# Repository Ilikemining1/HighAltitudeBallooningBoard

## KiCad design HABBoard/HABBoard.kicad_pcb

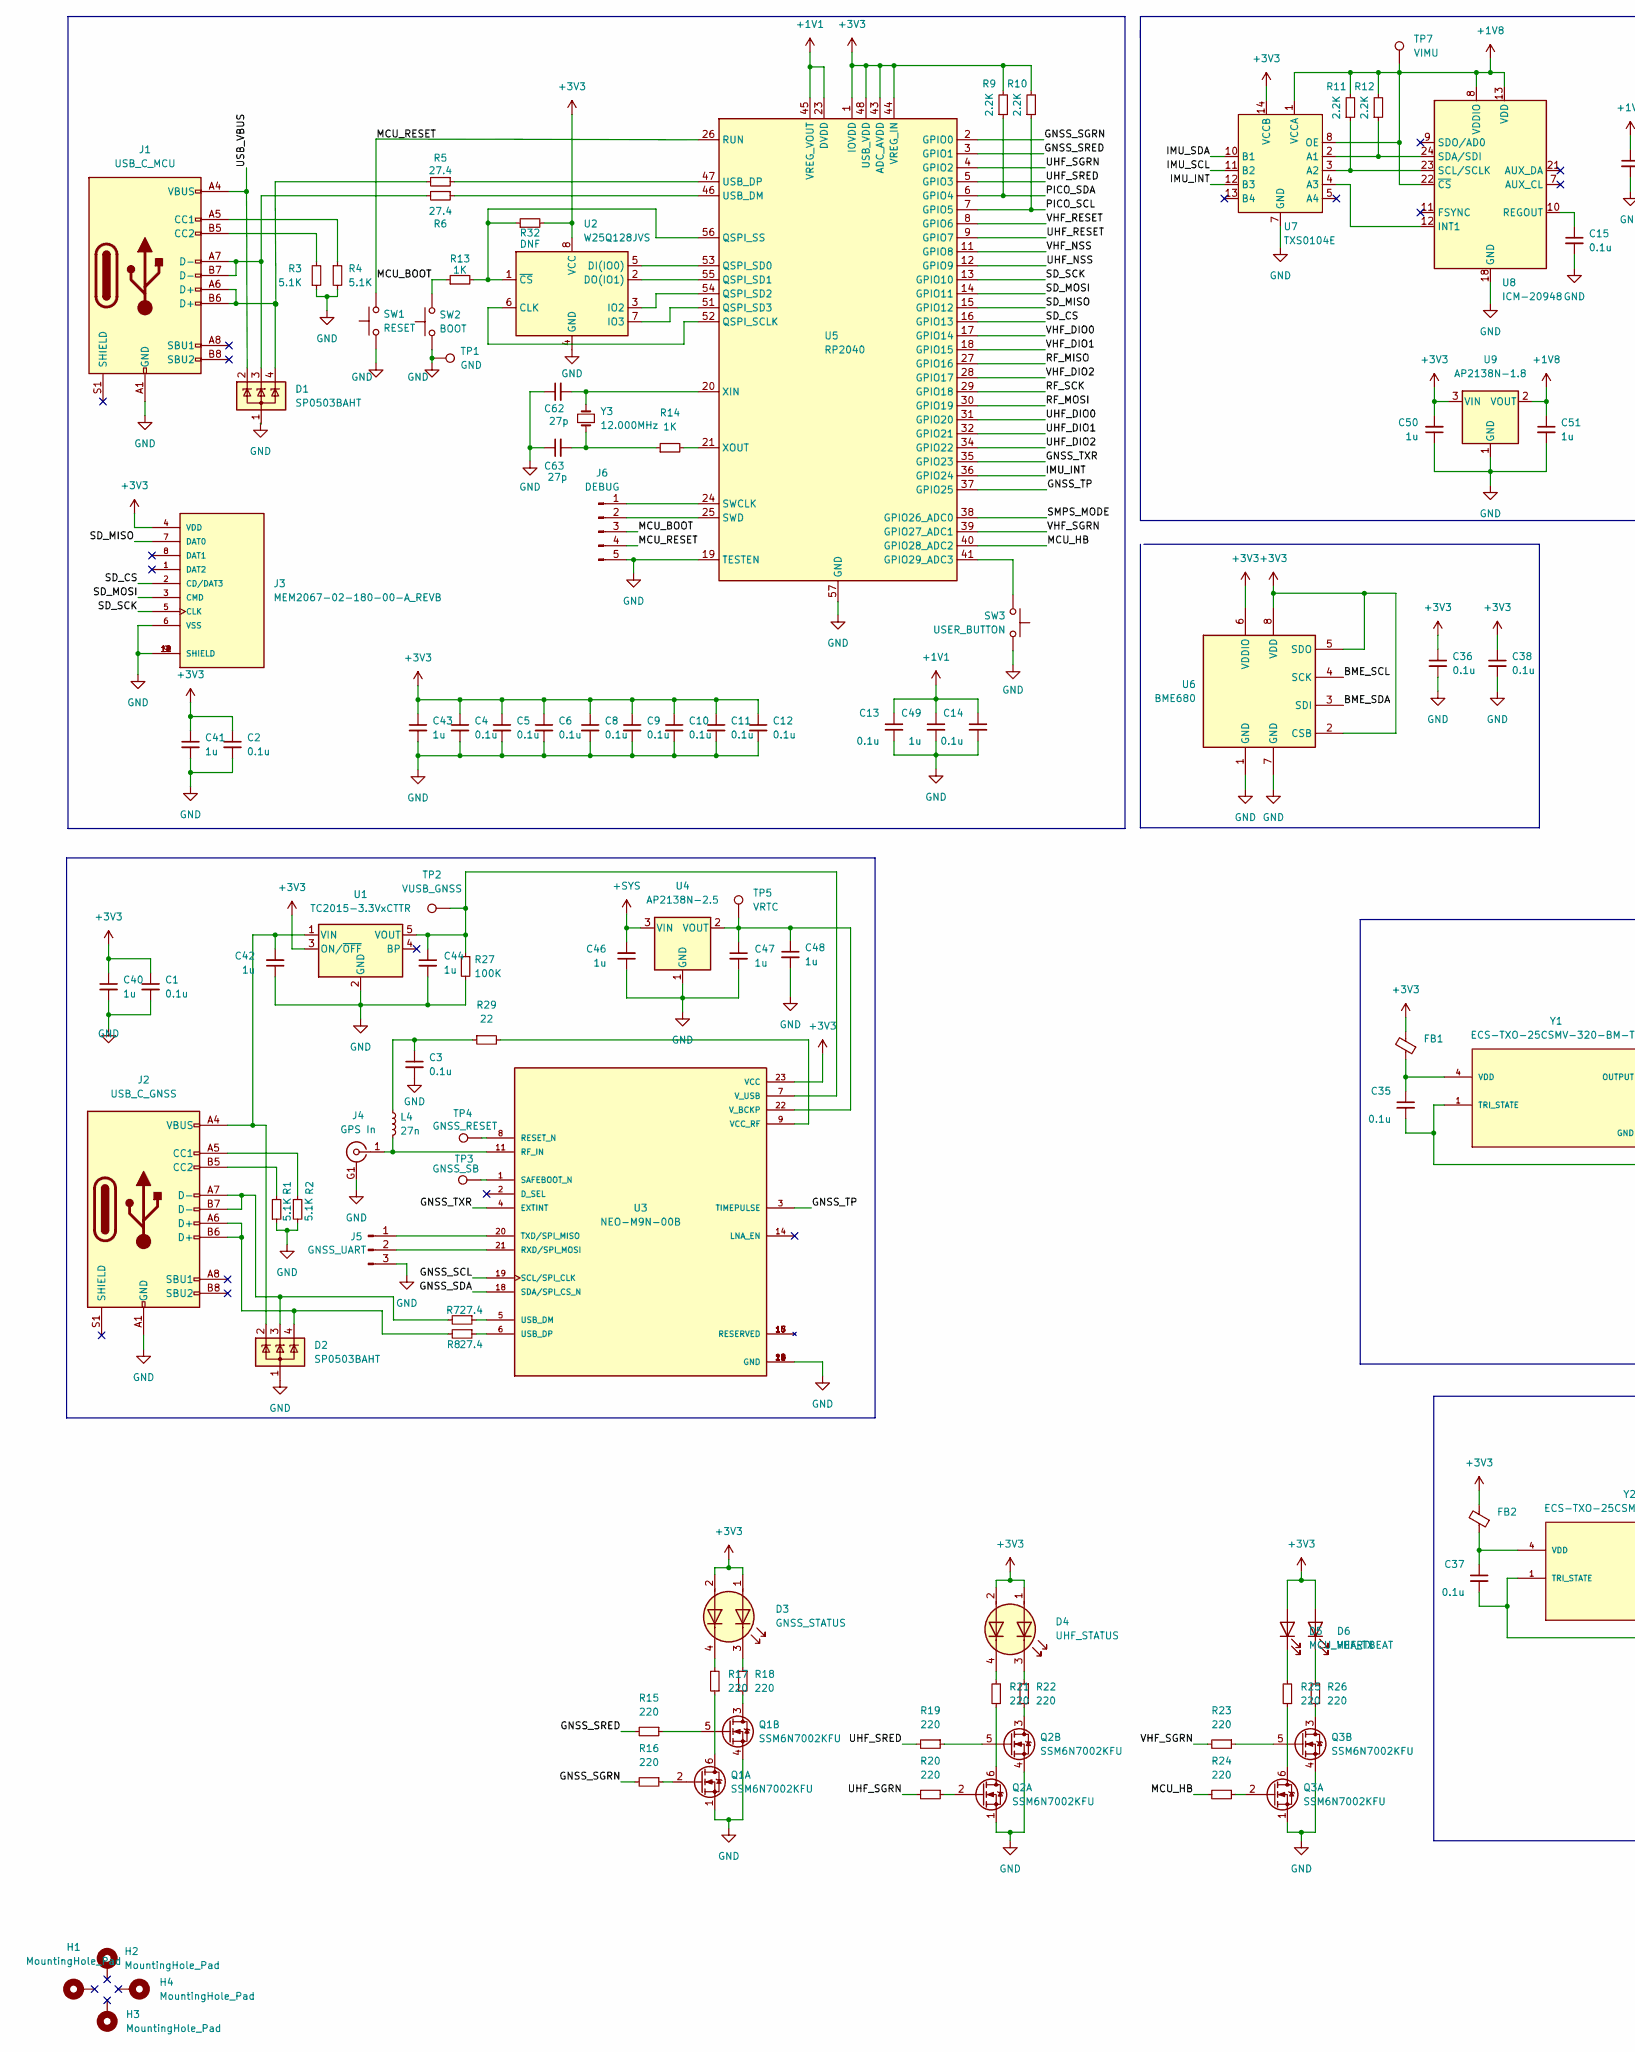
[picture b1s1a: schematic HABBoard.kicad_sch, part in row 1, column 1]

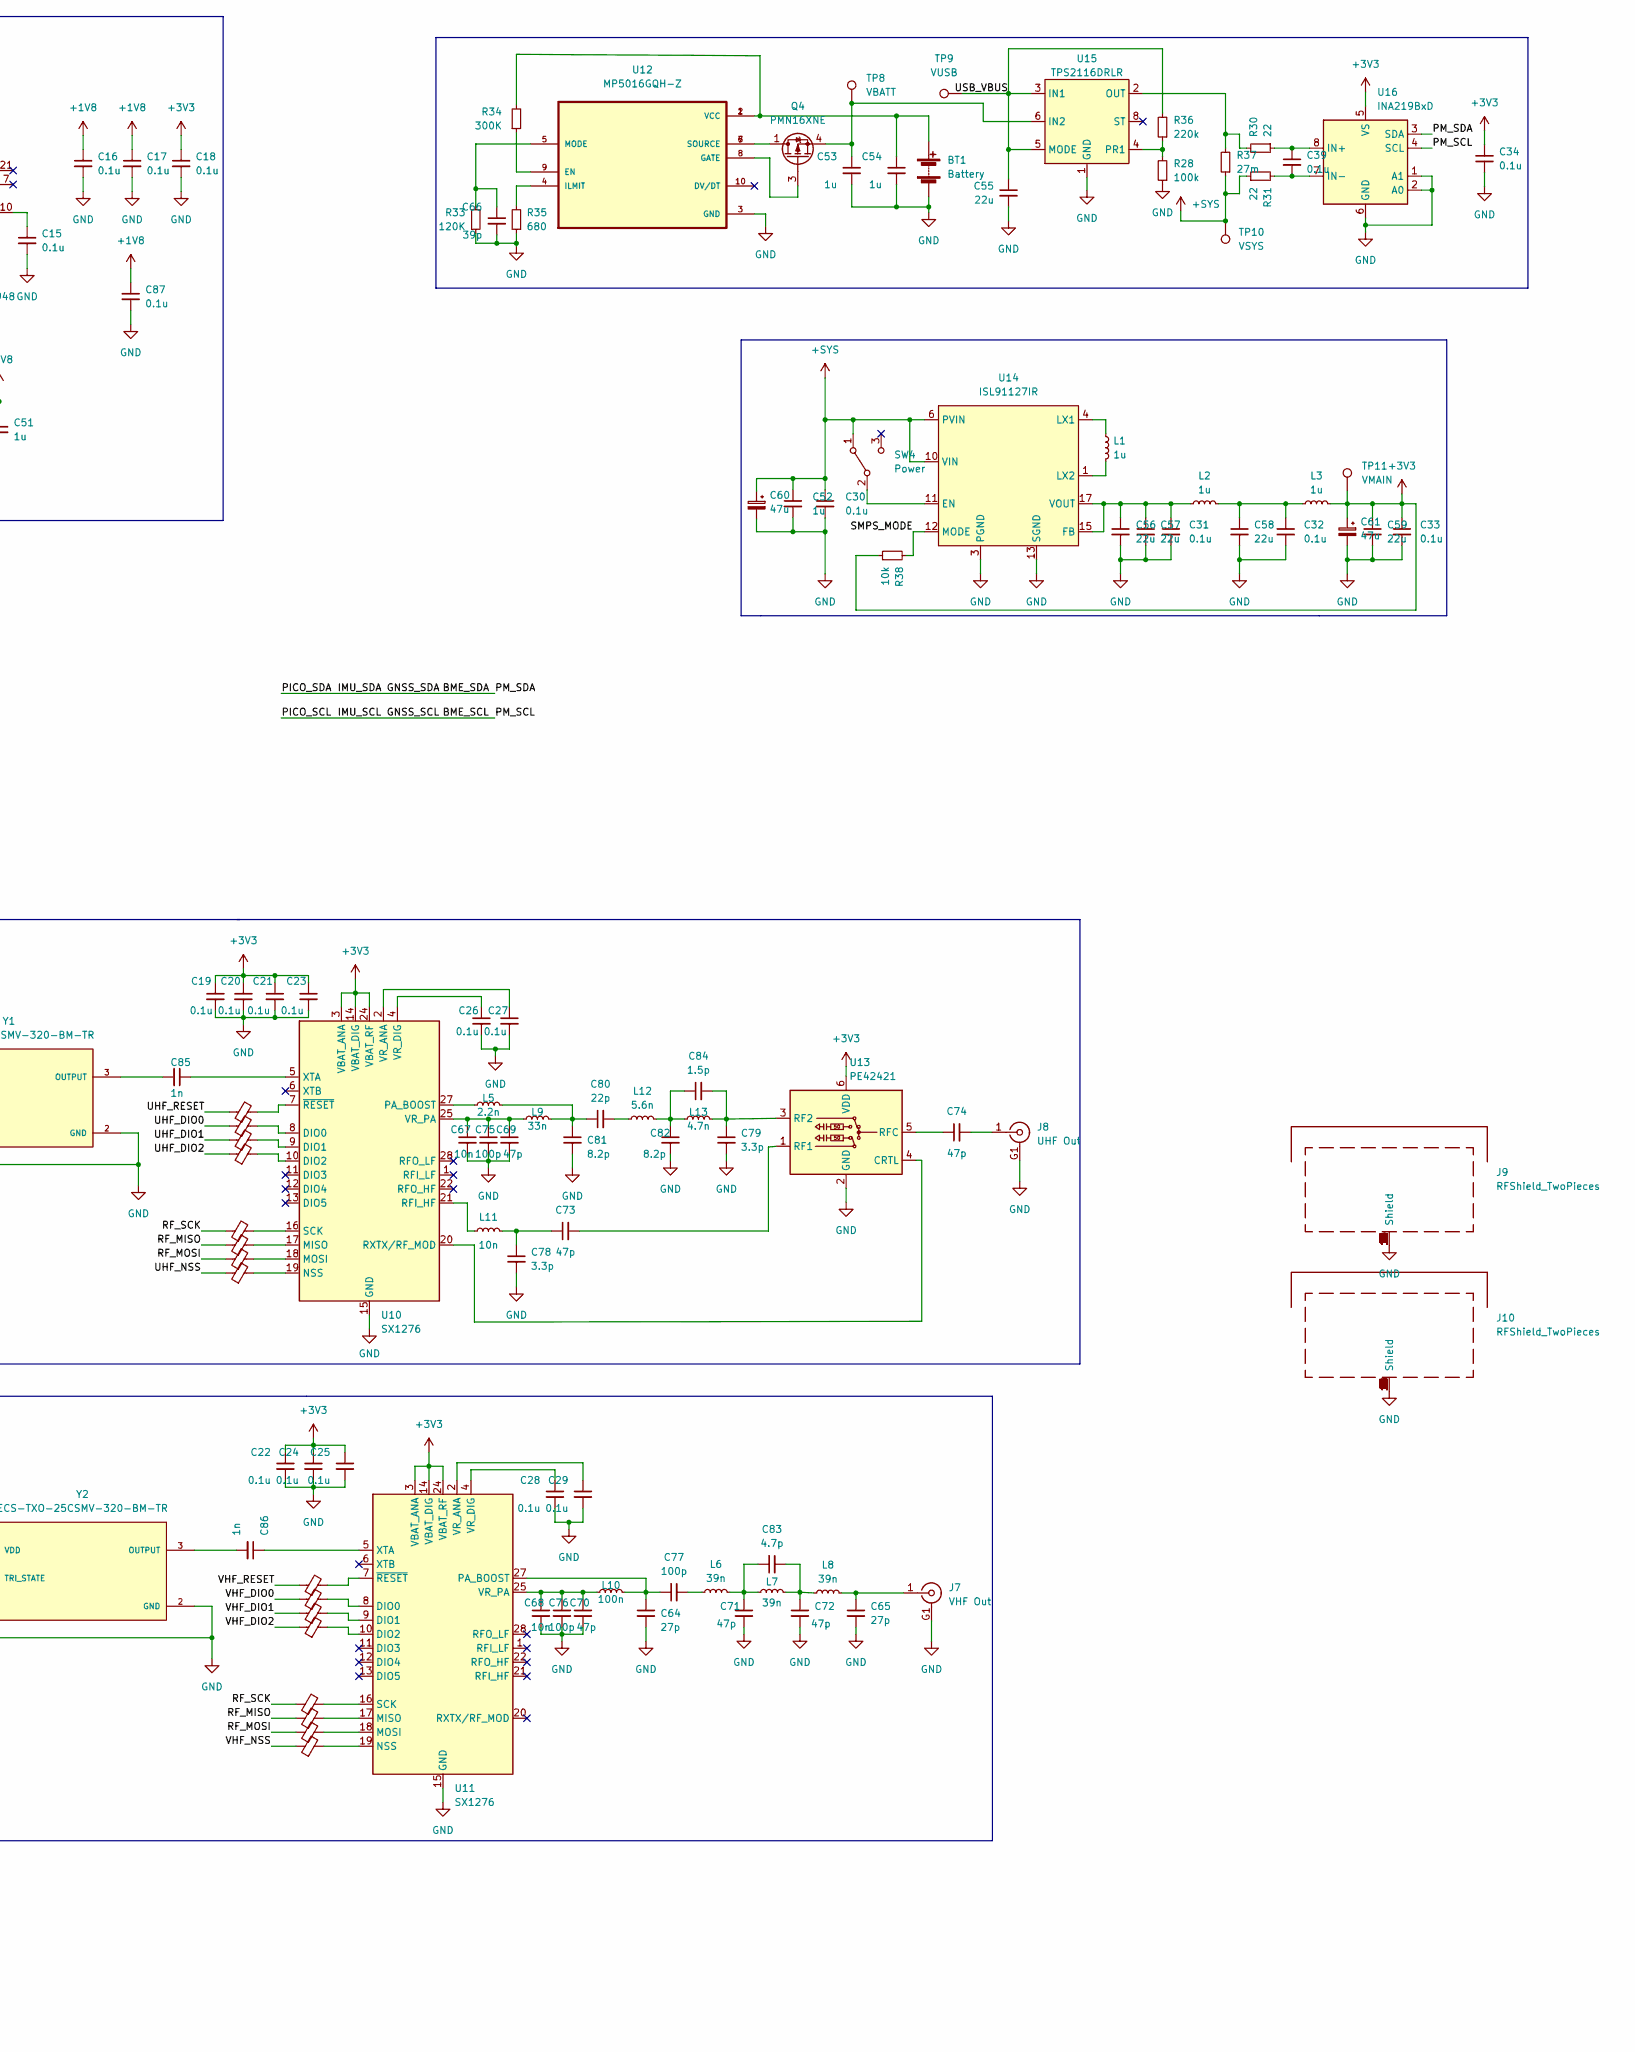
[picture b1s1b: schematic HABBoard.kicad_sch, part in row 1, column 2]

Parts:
BT1: Battery; CUI_TB002-500-02BE
C1, C2, C3, C4, C5, C6, C8, C9, C10, C11, C12, C13, C14, C15, C16, C17, C18, C19, C20, C21, C22, C23, C24, C25, C26, C27, C28, C29, C30, C31, C32, C33, C34, C35, C36, C37, C38, C39, C87: 0.1u; C_0402_1005Metric
C40, C41, C42, C43, C44, C46, C47, C48, C49, C50, C51, C52, C53, C54: 1u; C_0603_1608Metric
C55, C56, C57, C58, C59: 22u; C_0805_2012Metric
C60, C61: 47u; CP_Elec_5x5.3
C62, C63, C64, C65: 27p; C_0402_1005Metric
C66: 39p; C_0402_1005Metric
C67, C68: 10n; C_0402_1005Metric
C69, C70, C71, C72, C73, C74: 47p; C_0402_1005Metric
C75, C76, C77: 100p; C_0402_1005Metric
C78, C79: 3.3p; C_0402_1005Metric
C80: 22p; C_0402_1005Metric
C81, C82: 8.2p; C_0402_1005Metric
C83: 4.7p; C_0402_1005Metric
C84: 1.5p; C_0402_1005Metric
C85, C86: 1n; C_0402_1005Metric
D1, D2: SP0503BAHT; SOT-143
D3: GNSS_STATUS; LED_RGB_Wuerth-PLCC4_3.2x2.8mm_150141M173100
D4: UHF_STATUS; LED_RGB_Wuerth-PLCC4_3.2x2.8mm_150141M173100
D5: MCU_HEARTBEAT; LED_0603_1608Metric
D6: VHF_TX; LED_0603_1608Metric
FB1, FB2, FB3, FB4, FB5, FB7, FB8, FB9, FB10, FB11, FB12, FB13, FB14, FB15, FB16, FB17, FB18: FerriteBead_Small; L_0402_1005Metric
FB6: FB; L_0402_1005Metric
H1, H2, H3, H4: MountingHole_Pad; MountingHole_3.2mm_M3_Pad
J1: USB_C_MCU; USB_C_Receptacle_GCT_USB4085
J2: USB_C_GNSS; USB_C_Receptacle_GCT_USB4085
J3: MEM2067-02-180-00-A_REVB; GCT_MEM2067-02-180-00-A_REVB
J4: GPS In; LPRS_SMA_CONNECTOR
J5: GNSS_UART; PinHeader_1x03_P2.54mm_Vertical
J6: DEBUG; PinHeader_1x05_P2.54mm_Vertical
J7: VHF Out; LPRS_SMA_CONNECTOR
J8: UHF Out; LPRS_SMA_CONNECTOR
J9, J10: RFShield_TwoPieces; SMS409F
L1, L2, L3: 1u; L_Coilcraft_XxL4020
L4: 27n; L_0402_1005Metric
L5: 2.2n; L_0402_1005Metric
L6, L7, L8: 39n; L_0402_1005Metric
L9: 33n; L_0402_1005Metric
L10: 100n; L_0402_1005Metric
L11: 10n; L_0402_1005Metric
L12: 5.6n; L_0402_1005Metric
L13: 4.7n; L_0402_1005Metric
Q1, Q2, Q3: SSM6N7002KFU; SOT-363_SC-70-6
Q4: PMN16XNE; TSOP-6_1.65x3.05mm_P0.95mm
R1, R2, R3, R4: 5.1K; R_0402_1005Metric
R5, R6, R7, R8: 27.4; R_0402_1005Metric
R9, R10, R11, R12: 2.2K; R_0402_1005Metric
R13, R14: 1K; R_0402_1005Metric
R15, R16, R17, R18, R19, R20, R21, R22, R23, R24, R25, R26: 220; R_0402_1005Metric
R27: 100K; R_0402_1005Metric
R28: 100k; R_0402_1005Metric
R29, R30, R31: 22; R_0402_1005Metric
R32: DNF; R_0402_1005Metric
R33: 120K; R_0402_1005Metric
R34: 300K; R_0402_1005Metric
R35: 680; R_0402_1005Metric
R36: 220k; R_0402_1005Metric
R37: 27m; R_1206_3216Metric
R38: 10k; R_0402_1005Metric
SW1: RESET; PTS815SJK250SMTRLFS
SW2: BOOT; PTS815SJK250SMTRLFS
SW3: USER_BUTTON; PTS815SJK250SMTRLFS
SW4: Power; SW_JS102011SCQN
TP1: GND; TestPoint_Pad_D1.0mm
TP2: VUSB_GNSS; TestPoint_Pad_D1.0mm
TP3: GNSS_SB; TestPoint_Pad_D1.0mm
TP4: GNSS_RESET; TestPoint_Pad_D1.0mm
TP5: VRTC; TestPoint_Pad_D1.0mm
TP7: VIMU; TestPoint_Pad_D1.0mm
TP8: VBATT; TestPoint_Pad_D1.0mm
TP9: VUSB; TestPoint_Pad_D1.0mm
TP10: VSYS; TestPoint_Pad_D1.0mm
TP11: VMAIN; TestPoint_Pad_D1.0mm
U1: TC2015-3.3VxCTTR; SOT-23-5
U2: W25Q128JVS; SOIC-8_5.23x5.23mm_P1.27mm
U3: NEO-M9N-00B; XCVR_NEO-M9N-00B
U4: AP2138N-2.5; SOT-23
U5: RP2040; QFN-56-1EP_7x7mm_P0.4mm_EP3.2x3.2mm
U6: BME680; Bosch_LGA-8_3x3mm_P0.8mm_ClockwisePinNumbering
U7: TXS0104E; TSSOP-14_4.4x5mm_P0.65mm
U8: ICM-20948; InvenSense_QFN-24_3x3mm_P0.4mm
U9: AP2138N-1.8; SOT-23
U10, U11: SX1276; QFN-28-1EP_6x6mm_P0.65mm_EP4.8x4.8mm
U12: MP5016GQH-Z
U13: PE42421; SOT-363_SC-70-6
U14: ISL91127IR; QFN-20-1EP_4x4mm_P0.5mm_EP2.7x2.7mm_ThermalVias
U15: TPS2116DRLR; SOTFL50P160X60-8N
U16: INA219BxD; SOIC-8_3.9x4.9mm_P1.27mm
Y1, Y2: ECS-TXO-25CSMV-320-BM-TR; OSC_ECS-TXO-25CSMV-320-BM-TR
Y3: 12.000MHz; 445C25D12M00000

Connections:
+1V1: C13.1, C14.1, C49.1, U5.23 (DVDD), U5.45 (VREG_VOUT), U5.50 (DVDD)
+1V8: C16.1, C17.1, C51.1, C87.1, R11.2, R12.2, TP7.1, U7.1 (VCCA), U7.8 (OE), U8.8 (VDDIO), U8.13 (VDD), U8.22 (~CS), U9.2 (VOUT)
+3V3: C1.1, C2.1, C4.1, C5.1, C6.1, C8.1, C9.1, C10.1, C11.1, C12.1, C18.1, C19.1, C20.1, C21.1, C22.1, C23.1, C24.1, C25.1, C33.1, C34.1, C36.1, C38.1, C40.1, C41.1, C43.1, C50.2, C59.1, C61.1, D3.1 (A1), D3.2 (A2), D4.1 (A1), D4.2 (A2), D5.2 (A), D6.2 (A), FB1.2, FB2.2, J3.4 (VDD), L3.2, R9.2, R10.2, R32.2, R38.1, TP11.1, U1.3 (ON/~OFF), U2.8 (VCC), U3.23 (VCC), U5.1 (IOVDD), U5.10 (IOVDD), U5.22 (IOVDD), U5.33 (IOVDD), U5.42 (IOVDD), U5.43 (ADC_AVDD), U5.44 (VREG_IN), U5.48 (USB_VDD), U5.49 (IOVDD), U6.2 (CSB), U6.5 (SDO), U6.6 (VDDIO), U6.8 (VDD), U7.14 (VCCB), U9.3 (VIN), U10.3 (VBAT_ANA), U10.14 (VBAT_DIG), U10.24 (VBAT_RF), U11.3 (VBAT_ANA), U11.14 (VBAT_DIG), U11.24 (VBAT_RF), U13.6 (VDD), U16.5 (VS)
+SYS: C30.1, C46.2, C52.1, C60.1, R31.1, R37.1, SW4.1 (A), TP10.1, U4.3 (VIN), U14.6 (PVIN), U14.7 (PVIN), U14.8 (PVIN), U14.9 (PVIN), U14.10 (VIN)
/BME_SCL: R10.1, U3.19 (SCL/SPI_CLK), U5.7 (GPIO5), U6.4 (SCK), U7.11 (B2), U16.4 (SCL)
/BME_SDA: R9.1, U3.18 (SDA/SPI_CS_N), U5.6 (GPIO4), U6.3 (SDI), U7.10 (B1), U16.3 (SDA)
/GNSS_SGRN: R16.2, U5.2 (GPIO0)
/GNSS_SRED: R15.2, U5.3 (GPIO1)
/GNSS_TP: U3.3 (TIMEPULSE), U5.37 (GPIO25)
/GNSS_TXR: U3.4 (EXTINT), U5.35 (GPIO23)
/IMU_INT: U5.36 (GPIO24), U7.12 (B3)
/MCU_BOOT: J6.3, R13.1, SW2.2
/MCU_HB: R24.2, U5.40 (GPIO28_ADC2)
/MCU_RESET: J6.4, SW1.2, U5.26 (RUN)
/RF_MISO: FB4.1, FB12.1, U5.27 (GPIO16)
/RF_MOSI: FB5.1, FB13.1, U5.30 (GPIO19)
/RF_SCK: FB3.1, FB11.1, U5.29 (GPIO18)
/SD_CS: J3.2 (CD/DAT3), U5.16 (GPIO13)
/SD_MISO: J3.7 (DAT0), U5.15 (GPIO12)
/SD_MOSI: J3.3 (CMD), U5.14 (GPIO11)
/SD_SCK: J3.5 (CLK), U5.13 (GPIO10)
/SMPS_MODE: R38.2, U5.38 (GPIO26_ADC0), U14.12 (MODE)
/UHF_DIO0: FB8.1, U5.31 (GPIO20)
/UHF_DIO1: FB9.1, U5.32 (GPIO21)
/UHF_DIO2: FB10.1, U5.34 (GPIO22)
/UHF_NSS: FB6.1, U5.12 (GPIO9)
/UHF_RESET: FB7.1, U5.9 (GPIO7)
/UHF_SGRN: R20.2, U5.4 (GPIO2)
/UHF_SRED: R19.2, U5.5 (GPIO3)
/USB_VBUS: C55.1, D1.2 (K), J1.A4 (VBUS), J1.A9 (VBUS), J1.B4 (VBUS), J1.B9 (VBUS), R36.2, TP9.1, U15.3 (IN1), U15.5 (MODE)
/VHF_DIO0: FB16.1, U5.17 (GPIO14)
/VHF_DIO1: FB17.1, U5.18 (GPIO15)
/VHF_DIO2: FB18.1, U5.28 (GPIO17)
/VHF_NSS: FB14.1, U5.11 (GPIO8)
/VHF_RESET: FB15.1, U5.8 (GPIO6)
/VHF_SGRN: R23.2, U5.39 (GPIO27_ADC1)
GND: BT1.2 (-), C1.2, C2.2, C3.2, C4.2, C5.2, C6.2, C8.2, C9.2, C10.2, C11.2, C12.2, C13.2, C14.2, C15.2, C16.2, C17.2, C18.2, C19.2, C20.2, C21.2, C22.2, C23.2, C24.2, C25.2, C26.2, C27.2, C28.2, C29.2, C30.2, C31.2, C32.2, C33.2, C34.2, C35.2, C36.2, C37.2, C38.2, C40.2, C41.2, C42.1, C43.2, C44.2, C46.1, C47.2, C48.2, C49.2, C50.1, C51.2, C52.2, C53.2, C54.2, C55.2, C56.2, C57.2, C58.2, C59.2, C60.2, C61.2, C62.1, C63.1, C64.2, C65.2, C66.2, C67.2, C68.2, C69.2, C70.2, C71.2, C72.2, C75.2, C76.2, C78.2, C79.2, C81.2, C82.2, C87.2, D1.1 (A), D2.1 (A), J1.A1 (GND), J1.A12 (GND), J1.B1 (GND), J1.B12 (GND), J2.A1 (GND), J2.A12 (GND), J2.B1 (GND), J2.B12 (GND), J3.6 (VSS), J3.9 (SHIELD), J3.10 (SHIELD), J3.11 (SHIELD), J3.12 (SHIELD), J4.G1 (Ext), J4.G2 (Ext), J4.G3 (Ext), J4.G4 (Ext), J5.3, J6.5, J7.G1 (Ext), J7.G2 (Ext), J7.G3 (Ext), J7.G4 (Ext), J8.G1 (Ext), J8.G2 (Ext), J8.G3 (Ext), J8.G4 (Ext), J9.1 (Shield), J9.2 (Shield), J9.3 (Shield), J9.4 (Shield), J9.5 (Shield), J9.6 (Shield), J9.7 (Shield), J9.8 (Shield), J9.9 (Shield), J9.10 (Shield), J9.11 (Shield), J9.12 (Shield), J9.13 (Shield), J9.14 (Shield), J9.15 (Shield), J9.16 (Shield), J10.1 (Shield), J10.2 (Shield), J10.3 (Shield), J10.4 (Shield), J10.5 (Shield), J10.6 (Shield), J10.7 (Shield), J10.8 (Shield), J10.9 (Shield), J10.10 (Shield), J10.11 (Shield), J10.12 (Shield), J10.13 (Shield), J10.14 (Shield), J10.15 (Shield), J10.16 (Shield), Q1.1 (S), Q1.4 (S), Q2.1 (S), Q2.4 (S), Q3.1 (S), Q3.4 (S), R1.1, R2.2, R3.1, R4.2, R27.2, R28.1, R33.1, R35.1, SW1.1, SW2.1, SW3.1, TP1.1, U1.2 (GND), U2.4 (GND), U3.10 (GND), U3.12 (GND), U3.13 (GND), U3.24 (GND), U4.1 (GND), U5.19 (TESTEN), U5.57 (GND), U6.1 (GND), U6.7 (GND), U7.7 (GND), U8.18 (GND), U8.20 (GND), U9.1 (GND), U10.15 (GND), U10.23 (GND), U10.26 (GND), U10.29 (GND), U11.15 (GND), U11.23 (GND), U11.26 (GND), U11.29 (GND), U12.3 (GND), U13.2 (GND), U14.3 (PGND), U14.13 (SGND), U14.14 (SGND), U14.21 (PGND), U15.1 (GND), U16.1 (A1), U16.2 (A0), U16.6 (GND), Y1.1 (TRI_STATE), Y1.2 (GND), Y2.1 (TRI_STATE), Y2.2 (GND)
unnamed: BT1.1 (+), C54.1, R34.2, U12.1 (VCC), U12.2 (VCC)
unnamed: C3.1, L4.1, R29.1
unnamed: C15.1, U8.10 (REGOUT)
unnamed: C26.1, U10.4 (VR_DIG)
unnamed: C27.1, U10.2 (VR_ANA)
unnamed: C28.1, U11.4 (VR_DIG)
unnamed: C29.1, U11.2 (VR_ANA)
unnamed: C31.1, C56.1, C57.1, L2.1, U14.15 (FB), U14.17 (VOUT), U14.18 (VOUT), U14.19 (VOUT), U14.20 (VOUT)
unnamed: C32.1, C58.1, L2.2, L3.1
unnamed: C35.1, FB1.1, Y1.4 (VDD)
unnamed: C37.1, FB2.1, Y2.4 (VDD)
unnamed: C39.1, R30.1, U16.8 (IN+)
unnamed: C39.2, R31.2, U16.7 (IN-)
unnamed: C42.2, D2.2 (K), J2.A4 (VBUS), J2.A9 (VBUS), J2.B4 (VBUS), J2.B9 (VBUS), U1.1 (VIN)
unnamed: C44.1, R27.1, TP2.1, U1.5 (VOUT), U3.7 (V_USB)
unnamed: C47.1, C48.1, TP5.1, U3.22 (V_BCKP), U4.2 (VOUT)
unnamed: C53.1, Q4.4 (S), TP8.1, U15.6 (IN2)
unnamed: C62.2, U5.20 (XIN), Y3.2
unnamed: C63.2, R14.1, Y3.1
unnamed: C64.1, C77.1, L10.2, U11.27 (PA_BOOST)
unnamed: C65.1, J7.1 (In), L8.2
unnamed: C66.1, R33.2, U12.5 (MODE)
unnamed: C67.1, C69.1, C75.1, L9.1, U10.25 (VR_PA)
unnamed: C68.1, C70.1, C76.1, L10.1, U11.25 (VR_PA)
unnamed: C71.1, C83.1, L6.2, L7.1
unnamed: C72.1, C83.2, L7.2, L8.1
unnamed: C73.1, C78.1, L11.2
unnamed: C73.2, U13.1 (RF1)
unnamed: C74.1, U13.5 (RFC)
unnamed: C74.2, J8.1 (In)
unnamed: C77.2, L6.1
unnamed: C79.1, C84.2, L13.2, U13.3 (RF2)
unnamed: C80.1, C81.1, L5.2, L9.2
unnamed: C80.2, L12.1
unnamed: C82.1, C84.1, L12.2, L13.1
unnamed: C85.1, U10.5 (XTA)
unnamed: C85.2, Y1.3 (OUTPUT)
unnamed: C86.1, U11.5 (XTA)
unnamed: C86.2, Y2.3 (OUTPUT)
unnamed: D1.3 (K), J1.A7 (D-), J1.B7 (D-), R6.2
unnamed: D1.4 (K), J1.A6 (D+), J1.B6 (D+), R5.2
unnamed: D2.3 (K), J2.A7 (D-), J2.B7 (D-), R7.2
unnamed: D2.4 (K), J2.A6 (D+), J2.B6 (D+), R8.2
unnamed: D3.3 (K1), R18.1
unnamed: D3.4 (K2), R17.2
unnamed: D4.3 (K1), R22.1
unnamed: D4.4 (K2), R21.2
unnamed: D5.1 (K), R25.2
unnamed: D6.1 (K), R26.1
unnamed: FB3.2, U10.16 (SCK)
unnamed: FB4.2, U10.17 (MISO)
unnamed: FB5.2, U10.18 (MOSI)
unnamed: FB6.2, U10.19 (NSS)
unnamed: FB7.2, U10.7 (~RESET)
unnamed: FB8.2, U10.8 (DIO0)
unnamed: FB9.2, U10.9 (DIO1)
unnamed: FB10.2, U10.10 (DIO2)
unnamed: FB11.2, U11.16 (SCK)
unnamed: FB12.2, U11.17 (MISO)
unnamed: FB13.2, U11.18 (MOSI)
unnamed: FB14.2, U11.19 (NSS)
unnamed: FB15.2, U11.7 (~RESET)
unnamed: FB16.2, U11.8 (DIO0)
unnamed: FB17.2, U11.9 (DIO1)
unnamed: FB18.2, U11.10 (DIO2)
unnamed: J1.A5 (CC1), R4.1
unnamed: J1.B5 (CC2), R3.2
unnamed: J2.A5 (CC1), R2.1
unnamed: J2.B5 (CC2), R1.2
unnamed: J4.1 (In), L4.2, U3.11 (RF_IN)
unnamed: J5.1, U3.20 (TXD/SPI_MISO)
unnamed: J5.2, U3.21 (RXD/SPI_MOSI)
unnamed: J6.1, U5.24 (SWCLK)
unnamed: J6.2, U5.25 (SWD)
unnamed: L1.1, U14.4 (LX1), U14.5 (LX1)
unnamed: L1.2, U14.1 (LX2), U14.2 (LX2)
unnamed: L5.1, U10.27 (PA_BOOST)
unnamed: L11.1, U10.21 (RFI_HF)
unnamed: Q1.2 (G), R16.1
unnamed: Q1.3 (D), R18.2
unnamed: Q1.5 (G), R15.1
unnamed: Q1.6 (D), R17.1
unnamed: Q2.2 (G), R20.1
unnamed: Q2.3 (D), R22.2
unnamed: Q2.5 (G), R19.1
unnamed: Q2.6 (D), R21.1
unnamed: Q3.2 (G), R24.1
unnamed: Q3.3 (D), R26.2
unnamed: Q3.5 (G), R23.1
unnamed: Q3.6 (D), R25.1
unnamed: Q4.1 (D), Q4.2 (D), Q4.5 (D), Q4.6 (D), U12.6 (SOURCE), U12.7 (SOURCE)
unnamed: Q4.3 (G), U12.8 (GATE)
unnamed: R5.1, U5.47 (USB_DP)
unnamed: R6.1, U5.46 (USB_DM)
unnamed: R7.1, U3.5 (USB_DM)
unnamed: R8.1, U3.6 (USB_DP)
unnamed: R11.1, U7.3 (A2), U8.23 (SCL/SCLK)
unnamed: R12.1, U7.2 (A1), U8.24 (SDA/SDI)
unnamed: R13.2, R32.1, U2.1 (~CS), U5.56 (QSPI_SS)
unnamed: R14.2, U5.21 (XOUT)
unnamed: R28.2, R36.1, U15.4 (PR1)
unnamed: R29.2, U3.9 (VCC_RF)
unnamed: R30.2, R37.2, U15.2 (OUT), U15.7 (OUT)
unnamed: R34.1, U12.9 (EN)
unnamed: R35.2, U12.4 (ILMIT)
unnamed: SW3.2, U5.41 (GPIO29_ADC3)
unnamed: SW4.2 (B), U14.11 (EN)
unnamed: TP3.1, U3.1 (SAFEBOOT_N)
unnamed: TP4.1, U3.8 (RESET_N)
unnamed: U2.2 (DO(IO1)), U5.55 (QSPI_SD1)
unnamed: U2.3 (IO2), U5.54 (QSPI_SD2)
unnamed: U2.5 (DI(IO0)), U5.53 (QSPI_SD0)
unnamed: U2.6 (CLK), U5.52 (QSPI_SCLK)
unnamed: U2.7 (IO3), U5.51 (QSPI_SD3)
unnamed: U7.4 (A3), U8.12 (INT1)
unnamed: U10.20 (RXTX/RF_MOD), U13.4 (CRTL)

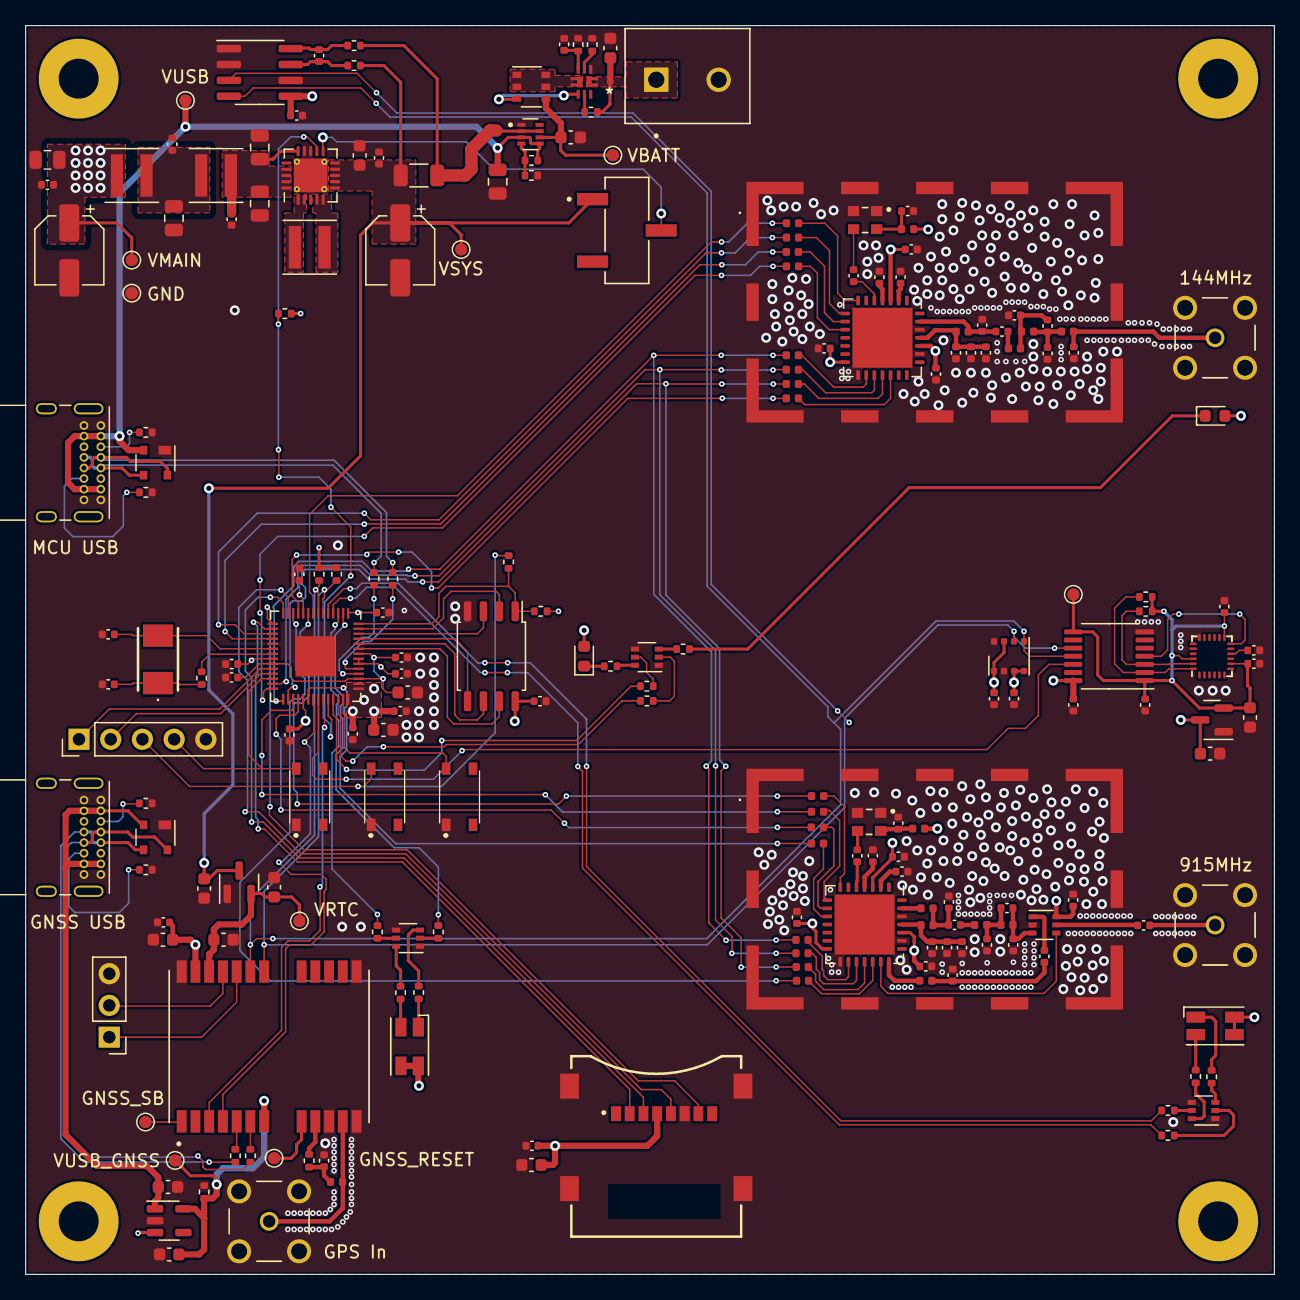
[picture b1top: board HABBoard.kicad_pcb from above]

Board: 4 copper layers, 100.0 x 100.0 mm, 212 parts (0 on the bottom side), 153 nets.

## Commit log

2022-12-27 Initial commit of PCB Files
2022-12-28 Added GPS Module
2023-01-06 Revisions before battery change
2023-01-08 Added the rest of the sensors
2023-01-08 Remove autosave
2023-01-14 RF Analog Design
2023-01-16 Add I2C address allocation table
2023-01-16 More RF Stuff
2023-01-16 Reorder table
2023-01-26 Last commit before sensor changes
2023-02-01 Update to BME688 sensor
2023-02-04 USB Mux Addition
2023-02-05 Added Power Switch IC, more filtering, and other stuff
2023-02-05 Final Schematic v1
2023-02-05 Final Schematic v2, begin footprint addition
2023-02-06 Adding Reference Designators, again...
2023-02-06 Update Schematic PDF
2023-02-06 Added footprints and 3D models for most parts in HABParts
2023-02-06 Schematic Annotation
2023-02-07 Mostly finished footprint association
2023-02-07 Footprint assignment complete
2023-02-08 Initial PCB Layout
2023-02-09 PCB Layout Work
2023-02-12 More trace routing
2023-02-19 More Routing
2023-02-23 Even more layout
2023-02-25 Finish majority of routing
2023-02-25 Update images and layout docs
2023-02-25 Fix PCB plane issues
2023-02-25 Add Gerbers
2023-02-26 Adjust RF Layout
2023-02-28 rearranged RF and more Via stitching
2023-02-28 Finalize PCB Design
2023-02-28 Update Imagery and Gerbers
2023-03-02 Finalize Design Files
2023-03-14 Add BOM
2023-03-23 Initial code commit
2023-03-28 Code updates and testing
2023-03-28 Code changes
2023-03-30 More code
2023-04-02 More code changes, ugly hacks implemented
    :
2023-04-02 New code
2023-04-16 Fixed dynamics issues
2023-04-17 Minor changes
